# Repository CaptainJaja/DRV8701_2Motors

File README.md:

# Driver DRV8701 – Dual H-Bridge 40 V / 10 A (15 A peak)

> PCB designed with **KiCad** for driving **two brushed DC motors** up to 40 V / 10 A.
> Each channel uses a TI **DRV8701** driver paired with four **TPH1R403NL** power MOSFETs.
> The board integrates **encoder feedback** for PID control, as well as **current regulation** handled directly by the DRV8701.
> The current limit is set to **3 A**: above this value, the driver applies **PWM current chopping** to maintain the current below the set point.

---

## ⭐ Sponsor: PCBWay

This project was **sponsored by PCBWay**, who kindly provided the PCBs for prototyping.
The PCB quality is excellent and the support very responsive.

👉 **PCBWay Link:**

Thanks again to Liam and the PCBWay team for their support!

---

## Main Specifications

| Parameter                | Value                                        |
| ------------------------ | -------------------------------------------- |
| Supply voltage VM        | 7 – 40 V                                     |
| Continuous current/motor | 10 A (4-layer PCB, 1 oz copper)              |
| Peak current             | 15 A (≤ 100 ms)                              |
| Chopped current limit    | 3 A (via DRV8701)                            |
| Topology                 | 2 × full H-bridge (DRV8701 + 4 MOSFETs each) |
| Control signals          | PH / EN / nSLEEP (TTL 3.3 V / 5 V)           |
| LED indication           | **EN** (active when nSLEEP = HIGH)           |
| NeoPixel indication      | Battery status (>25 V / 23–25 V / <23 V)     |
| PCB dimensions           | 100 mm × 40 mm                               |

---

## Thermal Management

* DRV8701 **exposed pad** connected to the GND plane through thermal vias.
* **TPH1R403NL (SOP-Advance)** MOSFETs soldered onto a large copper area + internal plane for heat spreading.
* Bulk decoupling capacitors: **470 µF / 50 V**, low ESR.

---

## PCB Views

### Component side

### Bottom copper side

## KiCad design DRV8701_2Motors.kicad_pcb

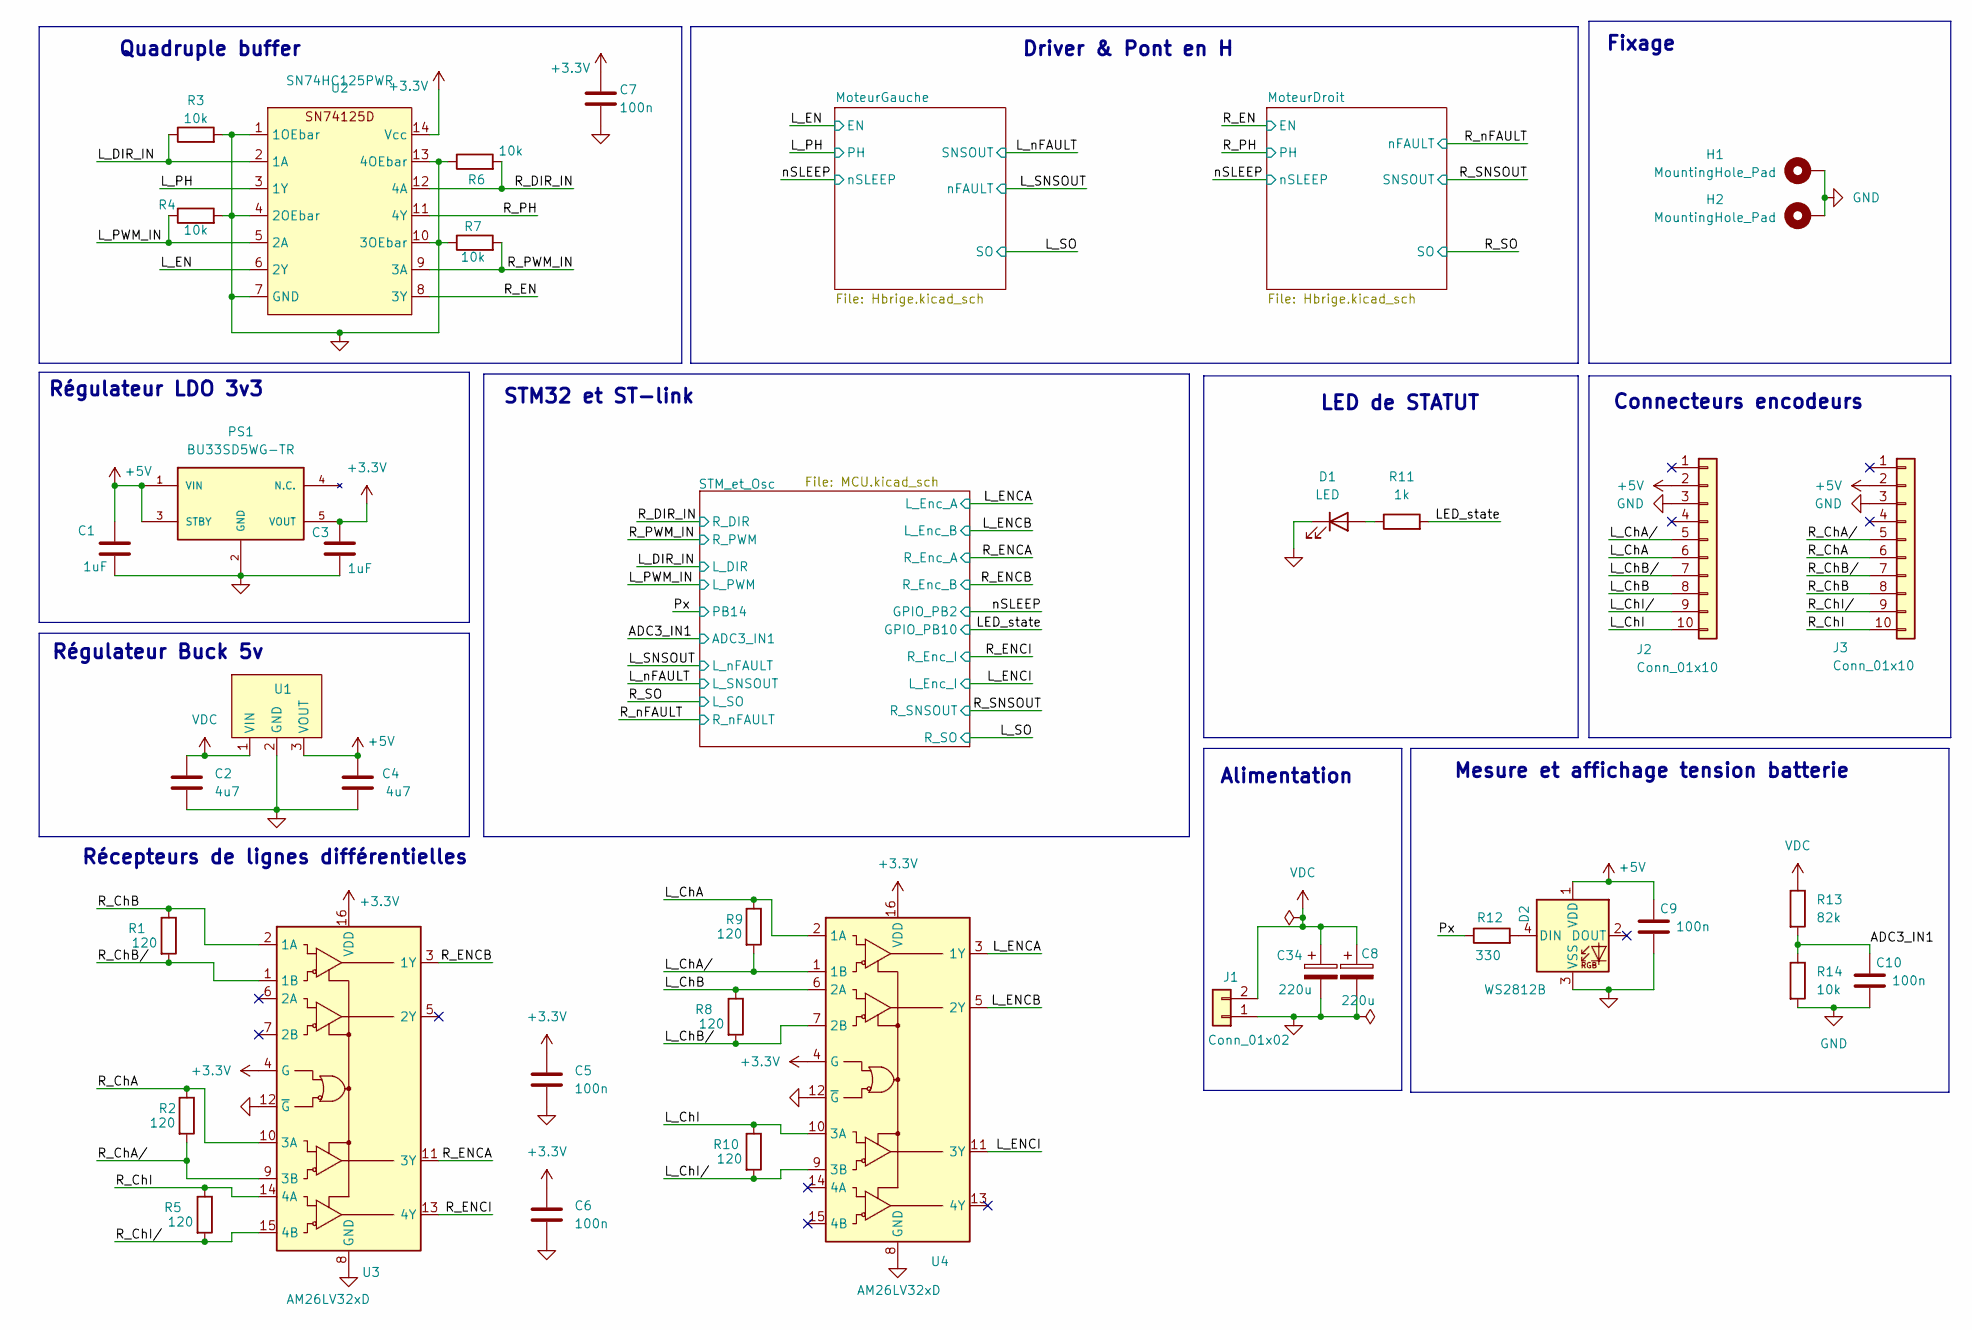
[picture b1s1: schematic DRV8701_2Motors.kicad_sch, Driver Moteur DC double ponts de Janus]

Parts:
C1, C3: 1uF; C_0603_1608Metric
C2: 4u7; C_1206_3216Metric
C4: 4u7; C_0603_1608Metric
C5, C6, C7, C9, C10: 100n; C_0402_1005Metric
C8, C34: 220u; ECA1HHG471
D1: LED; LED_0603_1608Metric_Pad1.05x0.95mm_HandSolder
D2: WS2812B; LED_WS2812B_PLCC4_5.0x5.0mm_P3.2mm
H1, H2: MountingHole_Pad; MountingHole_2.5mm_Pad
J1: Conn_01x02; KF301-5.0-2P
J2, J3: Conn_01x10; PinHeader_2x05_P1.27mm_Vertical_SMD
PS1: BU33SD5WG-TR; SOT95P280X125-5N; Mouser_Part_Number 755-BU33SD5WG-TR
R1, R2, R5, R8, R9, R10: 120; R_0402_1005Metric
R3, R4, R6, R7, R14: 10k; R_0402_1005Metric
R11: 1k; R_0402_1005Metric
R12: 330; R_0402_1005Metric
R13: 82k; R_0402_1005Metric
U1: StepDown3v3; MPN 173010x78
U2: SN74HC125PWR
U3, U4: AM26LV32xD; SOIC-16_3.9x9.9mm_P1.27mm

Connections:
+3.3V: C3.1, C5.1, C6.1, C7.1, PS1.5 (VOUT), U2.14 (Vcc), U3.4 (G), U3.16 (VDD), U4.4 (G), U4.16 (VDD); also elsewhere on the board
+5V: C1.1, C4.1, C9.2, D2.1 (VDD), J2.2, J3.2, PS1.1 (VIN), PS1.3 (STBY), U1.3 (VOUT)
/ADC3_IN1: C10.2, R13.2, R14.1; also elsewhere on the board
/LED_state: R11.2; also elsewhere on the board
/L_ChA: J2.6, R9.1, U4.2 (1A)
/L_ChA/: J2.5, R9.2, U4.1 (1B)
/L_ChB: J2.8, R8.1, U4.6 (2A)
/L_ChB/: J2.7, R8.2, U4.7 (2B)
/L_ChI: J2.10, R10.1, U4.10 (3A)
/L_ChI/: J2.9, R10.2, U4.9 (3B)
/L_DIR_IN: R3.1, U2.2 (1A); also elsewhere on the board
/L_EN: U2.6 (2Y); also elsewhere on the board
/L_ENCA: U4.3 (1Y); also elsewhere on the board
/L_ENCB: U4.5 (2Y); also elsewhere on the board
/L_ENCI: U4.11 (3Y); also elsewhere on the board
/L_PH: U2.3 (1Y); also elsewhere on the board
/L_PWM_IN: R4.1, U2.5 (2A); also elsewhere on the board
/Px: R12.1; also elsewhere on the board
/R_ChA: J3.6, R2.1, U3.10 (3A)
/R_ChA/: J3.5, R2.2, U3.9 (3B)
/R_ChB: J3.8, R1.1, U3.2 (1A)
/R_ChB/: J3.7, R1.2, U3.1 (1B)
/R_ChI: J3.10, R5.1, U3.14 (4A)
/R_ChI/: J3.9, R5.2, U3.15 (4B)
/R_DIR_IN: R6.2, U2.12 (4A); also elsewhere on the board
/R_EN: U2.8 (3Y); also elsewhere on the board
/R_ENCA: U3.11 (3Y); also elsewhere on the board
/R_ENCB: U3.3 (1Y); also elsewhere on the board
/R_ENCI: U3.13 (4Y); also elsewhere on the board
/R_PH: U2.11 (4Y); also elsewhere on the board
/R_PWM_IN: R7.2, U2.9 (3A); also elsewhere on the board
GND: C1.2, C2.2, C3.2, C4.2, C5.2, C6.2, C7.2, C8.2, C9.1, C10.1, C34.2, D1.1 (K), D2.3 (VSS), H1.1, H2.1, J1.1, J2.3, J3.3, PS1.2 (GND), R3.2, R4.2, R6.1, R7.1, R14.2, U1.2 (GND), U2.1 (1OEbar), U2.4 (2OEbar), U2.7 (GND), U2.10 (3OEbar), U2.13 (4OEbar), U3.8 (GND), U3.12 (~G), U4.8 (GND), U4.12 (~G); also elsewhere on the board
unnamed: D1.2 (A), R11.1
unnamed: D2.4 (DIN), R12.2
VDC: C2.1, C8.1, C34.1, J1.2, R13.1, U1.1 (VIN); also elsewhere on the board

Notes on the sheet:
STM32 et ST-link
Driver & Pont en H
Fixage
Quadruple buffer
Régulateur LDO 3v3
Connecteurs encodeurs
Alimentation
LED de STATUT
Récepteurs de lignes différentielles
Régulateur Buck 5v
Mesure et affichage tension batterie

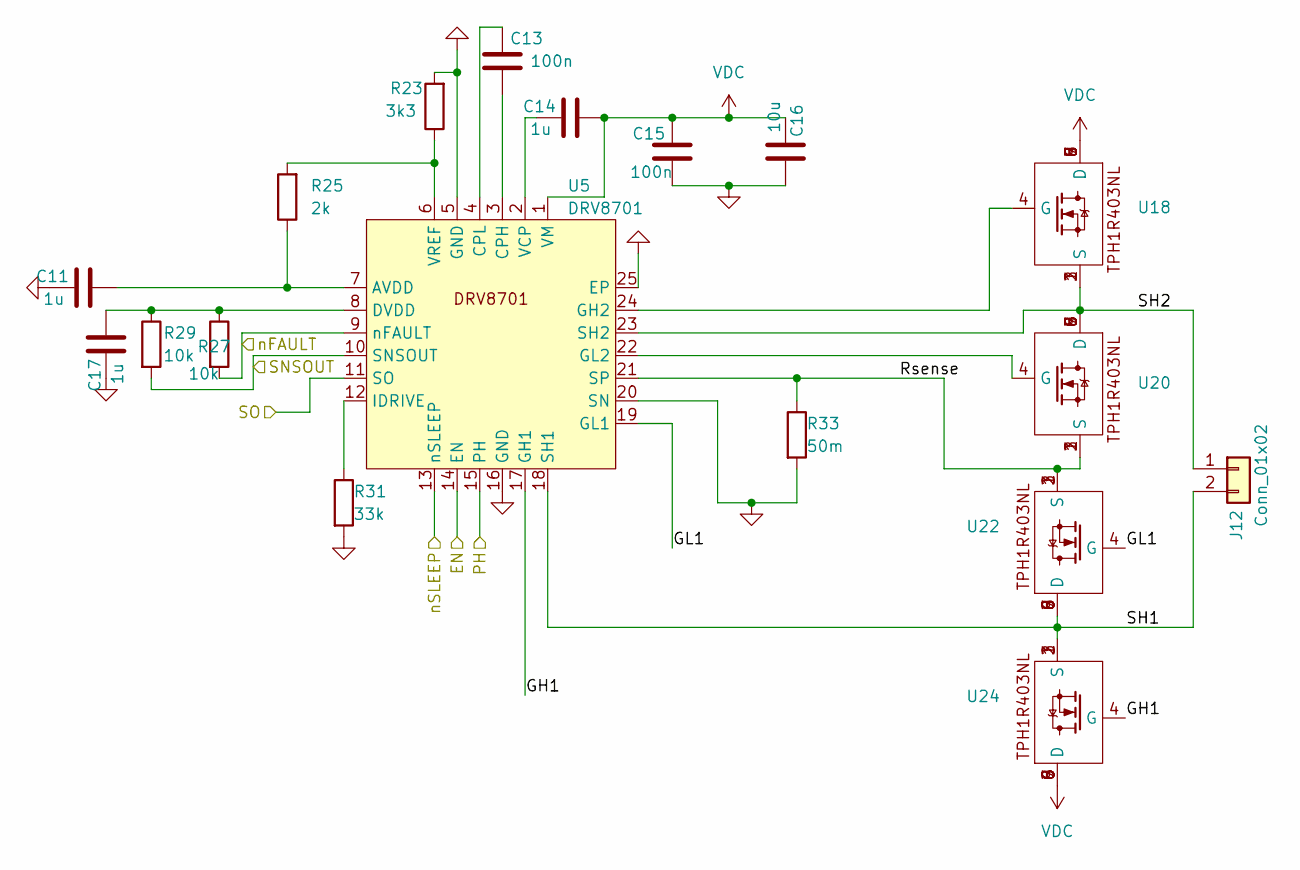
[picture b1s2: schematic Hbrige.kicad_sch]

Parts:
C11, C17: 1u; C_0603_1608Metric
C13, C15: 100n; C_0603_1608Metric
C14: 1u; C_0805_2012Metric
C16: 10u; C_1206_3216Metric
J12: Conn_01x02; KF301-5.0-2P
R23: 3k3; R_0402_1005Metric
R25: 2k; R_0402_1005Metric
R27, R29: 10k; R_0402_1005Metric
R31: 33k; R_0402_1005Metric
R33: 50m; R_2512_6332Metric
U5: DRV8701; DRV8701ERGER
U18, U20, U22, U24: TPH1R403NL; MPN TPH1R403NL

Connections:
/MoteurDroit/GH1: U5.17 (GH1), U24.4 (G)
/MoteurDroit/GL1: U5.19 (GL1), U22.4 (G)
/MoteurDroit/Rsense: R33.1, U5.21 (SP), U20.1 (S), U20.2 (S), U20.3 (S), U22.1 (S), U22.2 (S), U22.3 (S)
/MoteurDroit/SH1: J12.2, U5.18 (SH1), U22.5 (D), U22.6 (D), U22.7 (D), U22.8 (D), U22.9 (D), U24.1 (S), U24.2 (S), U24.3 (S)
/MoteurDroit/SH2: J12.1, U5.23 (SH2), U18.1 (S), U18.2 (S), U18.3 (S), U20.5 (D), U20.6 (D), U20.7 (D), U20.8 (D), U20.9 (D)
/R_EN: U5.14 (EN); also elsewhere on the board
/R_PH: U5.15 (PH); also elsewhere on the board
/R_SNSOUT: R29.2, U5.10 (SNSOUT); also elsewhere on the board
/R_SO: U5.11 (SO); also elsewhere on the board
/R_nFAULT: R27.2, U5.9 (nFAULT); also elsewhere on the board
/nSLEEP: U5.13 (nSLEEP); also elsewhere on the board
GND: C11.2, C15.1, C16.1, C17.2, R23.2, R31.2, R33.2, U5.5 (GND), U5.16 (GND), U5.20 (SN), U5.25 (EP); also elsewhere on the board
unnamed: C11.1, R25.1, U5.7 (AVDD)
unnamed: C13.1, U5.3 (CPH)
unnamed: C13.2, U5.4 (CPL)
unnamed: C17.1, R27.1, R29.1, U5.8 (DVDD)
unnamed: R31.1, U5.12 (IDRIVE)
unnamed: C14.2, U5.2 (VCP)
unnamed: R23.1, R25.2, U5.6 (VREF)
unnamed: U5.24 (GH2), U18.4 (G)
unnamed: U5.22 (GL2), U20.4 (G)
VDC: C14.1, C15.2, C16.2, U5.1 (VM), U18.5 (D), U18.6 (D), U18.7 (D), U18.8 (D), U18.9 (D), U24.5 (D), U24.6 (D), U24.7 (D), U24.8 (D), U24.9 (D); also elsewhere on the board

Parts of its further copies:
C12, C18: 1u; C_0603_1608Metric
C19, C21: 100n; C_0603_1608Metric
C20: 1u; C_0805_2012Metric
C22: 10u; C_1206_3216Metric
J13: Conn_01x02; KF301-5.0-2P
R24: 3k3; R_0402_1005Metric
R26: 2k; R_0402_1005Metric
R28, R30: 10k; R_0402_1005Metric
R32: 33k; R_0402_1005Metric
R34: 50m; R_2512_6332Metric
U10: DRV8701; DRV8701ERGER
U19, U21, U23, U25: TPH1R403NL; MPN TPH1R403NL

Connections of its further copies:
/L_EN: U10.14 (EN); also elsewhere on the board
/L_PH: U10.15 (PH); also elsewhere on the board
/L_SNSOUT: R28.2, U10.9 (nFAULT); also elsewhere on the board
/L_SO: U10.11 (SO); also elsewhere on the board
/L_nFAULT: R30.2, U10.10 (SNSOUT); also elsewhere on the board
/MoteurGauche/GH1: U10.17 (GH1), U25.4 (G)
/MoteurGauche/GL1: U10.19 (GL1), U23.4 (G)
/MoteurGauche/Rsense: R34.1, U10.21 (SP), U21.1 (S), U21.2 (S), U21.3 (S), U23.1 (S), U23.2 (S), U23.3 (S)
/MoteurGauche/SH1: J13.2, U10.18 (SH1), U23.5 (D), U23.6 (D), U23.7 (D), U23.8 (D), U23.9 (D), U25.1 (S), U25.2 (S), U25.3 (S)
/MoteurGauche/SH2: J13.1, U10.23 (SH2), U19.1 (S), U19.2 (S), U19.3 (S), U21.5 (D), U21.6 (D), U21.7 (D), U21.8 (D), U21.9 (D)
/nSLEEP: U10.13 (nSLEEP); also elsewhere on the board
GND: C12.2, C18.2, C21.1, C22.1, R24.2, R32.2, R34.2, U10.5 (GND), U10.16 (GND), U10.20 (SN), U10.25 (EP); also elsewhere on the board
unnamed: C12.1, R26.1, U10.7 (AVDD)
unnamed: C19.1, U10.3 (CPH)
unnamed: C19.2, U10.4 (CPL)
unnamed: C18.1, R28.1, R30.1, U10.8 (DVDD)
unnamed: U10.24 (GH2), U19.4 (G)
unnamed: U10.22 (GL2), U21.4 (G)
unnamed: R32.1, U10.12 (IDRIVE)
unnamed: C20.2, U10.2 (VCP)
unnamed: R24.1, R26.2, U10.6 (VREF)
VDC: C20.1, C21.2, C22.2, U10.1 (VM), U19.5 (D), U19.6 (D), U19.7 (D), U19.8 (D), U19.9 (D), U25.5 (D), U25.6 (D), U25.7 (D), U25.8 (D), U25.9 (D); also elsewhere on the board

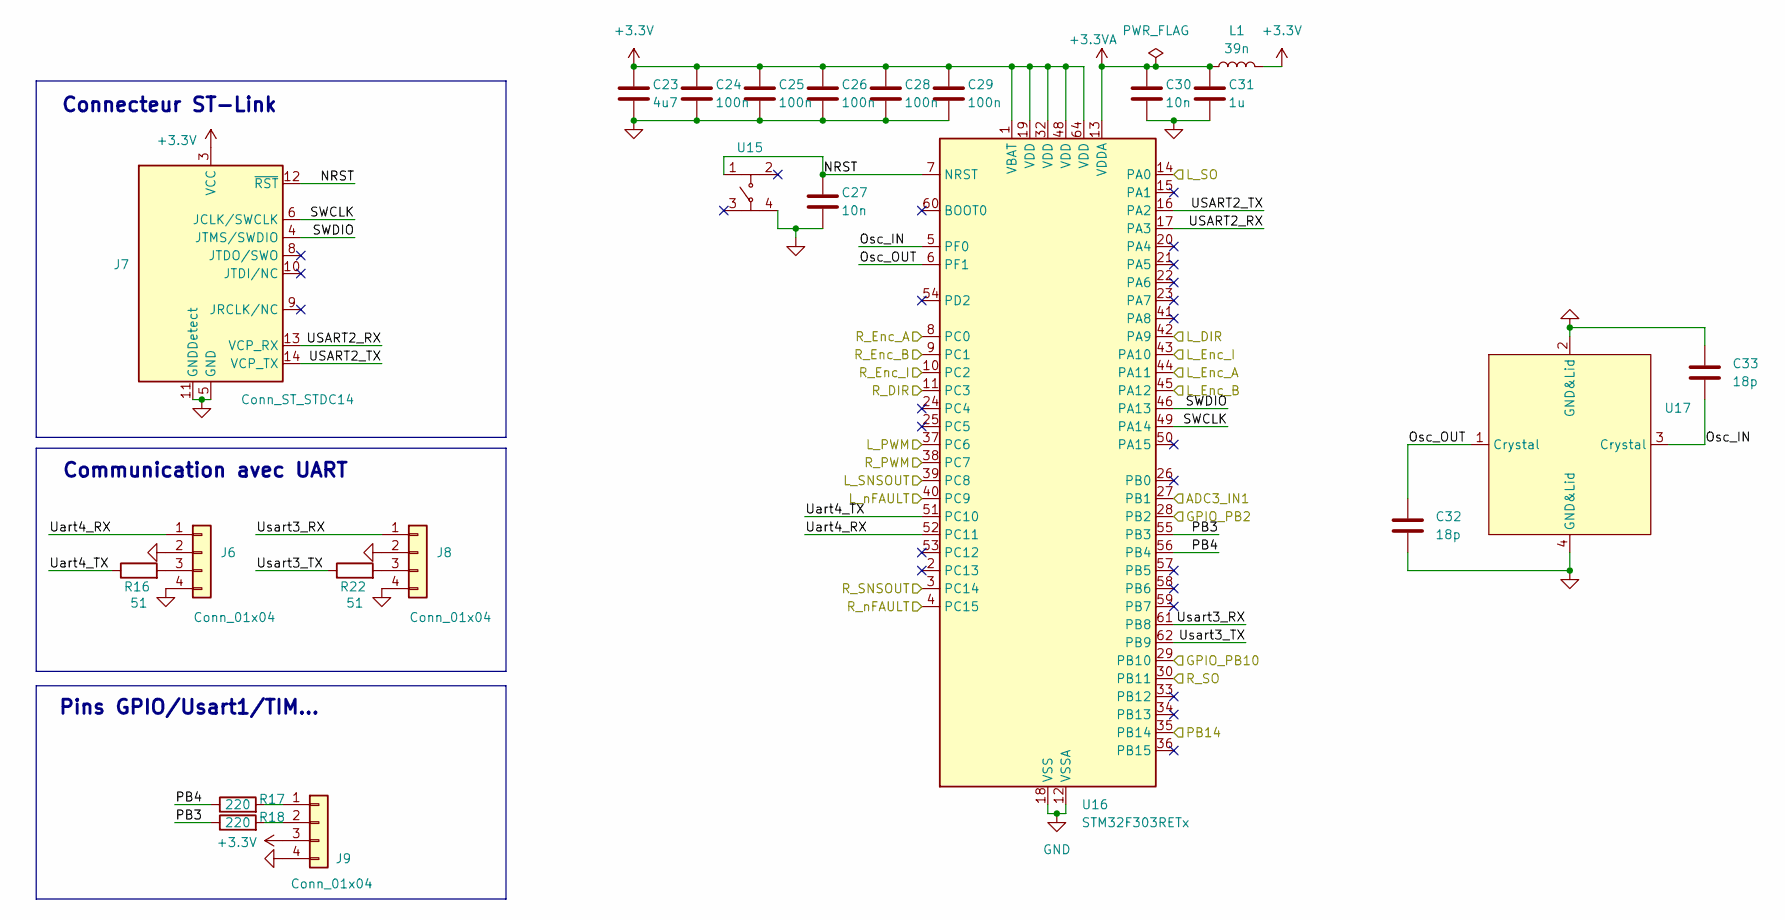
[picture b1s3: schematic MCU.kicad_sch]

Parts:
C23: 4u7; C_0402_1005Metric
C24, C25, C26, C28, C29: 100n; C_0402_1005Metric
C27, C30: 10n; C_0402_1005Metric
C31: 1u; C_0402_1005Metric
C32, C33: 18p; C_0603_1608Metric
J6, J8: Conn_01x04; JST_EH_B4B-EH-A_1x04_P2.50mm_Vertical
J7: Conn_ST_STDC14; PinHeader_2x07_P1.27mm_Vertical_SMD
J9: Conn_01x04; PinHeader_1x04_P2.54mm_Vertical
L1: 39n; L_0603_1608Metric
R16, R22: 51; R_0402_1005Metric
R17, R18: 220; R_0402_1005Metric
U15: WS-TASU SMT Tact Switch 4.7x3.5 mm side push
U16: STM32F303RETx; LQFP-64_10x10mm_P0.5mm
U17: Crystal_SMD_7050-4Pin_7.0x5.0mm

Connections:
+3.3V: C23.1, C24.1, C25.1, C26.1, C28.1, C29.1, J7.3 (VCC), J9.3, L1.2, U16.1 (VBAT), U16.19 (VDD), U16.32 (VDD), U16.48 (VDD), U16.64 (VDD); also elsewhere on the board
+3.3VA: C30.1, C31.1, L1.1, U16.13 (VDDA)
/ADC3_IN1: U16.27 (PB1); also elsewhere on the board
/LED_state: U16.29 (PB10); also elsewhere on the board
/L_DIR_IN: U16.42 (PA9); also elsewhere on the board
/L_ENCA: U16.44 (PA11); also elsewhere on the board
/L_ENCB: U16.45 (PA12); also elsewhere on the board
/L_ENCI: U16.43 (PA10); also elsewhere on the board
/L_PWM_IN: U16.37 (PC6); also elsewhere on the board
/L_SNSOUT: U16.40 (PC9); also elsewhere on the board
/L_SO: U16.30 (PB11); also elsewhere on the board
/L_nFAULT: U16.39 (PC8); also elsewhere on the board
/Px: U16.35 (PB14); also elsewhere on the board
/R_DIR_IN: U16.11 (PC3); also elsewhere on the board
/R_ENCA: U16.8 (PC0); also elsewhere on the board
/R_ENCB: U16.9 (PC1); also elsewhere on the board
/R_ENCI: U16.10 (PC2); also elsewhere on the board
/R_PWM_IN: U16.38 (PC7); also elsewhere on the board
/R_SNSOUT: U16.3 (PC14); also elsewhere on the board
/R_SO: U16.14 (PA0); also elsewhere on the board
/R_nFAULT: U16.4 (PC15); also elsewhere on the board
/STM_et_Osc/NRST: C27.1, J7.12 (~RST), U15.1, U16.7 (NRST)
/STM_et_Osc/Osc_IN: C33.2, U16.5 (PF0), U17.3 (Crystal)
/STM_et_Osc/Osc_OUT: C32.1, U16.6 (PF1), U17.1 (Crystal)
/STM_et_Osc/PB3: R18.1, U16.55 (PB3)
/STM_et_Osc/PB4: R17.1, U16.56 (PB4)
/STM_et_Osc/SWCLK: J7.6 (JCLK/SWCLK), U16.49 (PA14)
/STM_et_Osc/SWDIO: J7.4 (JTMS/SWDIO), U16.46 (PA13)
/STM_et_Osc/USART2_RX: J7.13 (VCP_RX), U16.17 (PA3)
/STM_et_Osc/USART2_TX: J7.14 (VCP_TX), U16.16 (PA2)
/STM_et_Osc/Uart4_RX: J6.1, U16.52 (PC11)
/STM_et_Osc/Uart4_TX: R16.1, U16.51 (PC10)
/STM_et_Osc/Usart3_RX: J8.1, U16.61 (PB8)
/STM_et_Osc/Usart3_TX: R22.1, U16.62 (PB9)
/nSLEEP: U16.28 (PB2); also elsewhere on the board
GND: C23.2, C24.2, C25.2, C26.2, C27.2, C28.2, C29.2, C30.2, C31.2, C32.2, C33.1, J6.2, J6.4, J7.5 (GND), J7.7 (GND), J7.11 (GNDDetect), J8.2, J8.4, J9.4, U15.4, U16.12 (VSSA), U16.18 (VSS), U16.31 (VSS), U16.47 (VSS), U16.63 (VSS), U17.2 (GND&Lid), U17.4 (GND&Lid); also elsewhere on the board
unnamed: J6.3, R16.2
unnamed: J8.3, R22.2
unnamed: J9.1, R17.2
unnamed: J9.2, R18.2

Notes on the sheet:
Pins GPIO/Usart1/TIM...
Communication avec UART
Connecteur ST-Link

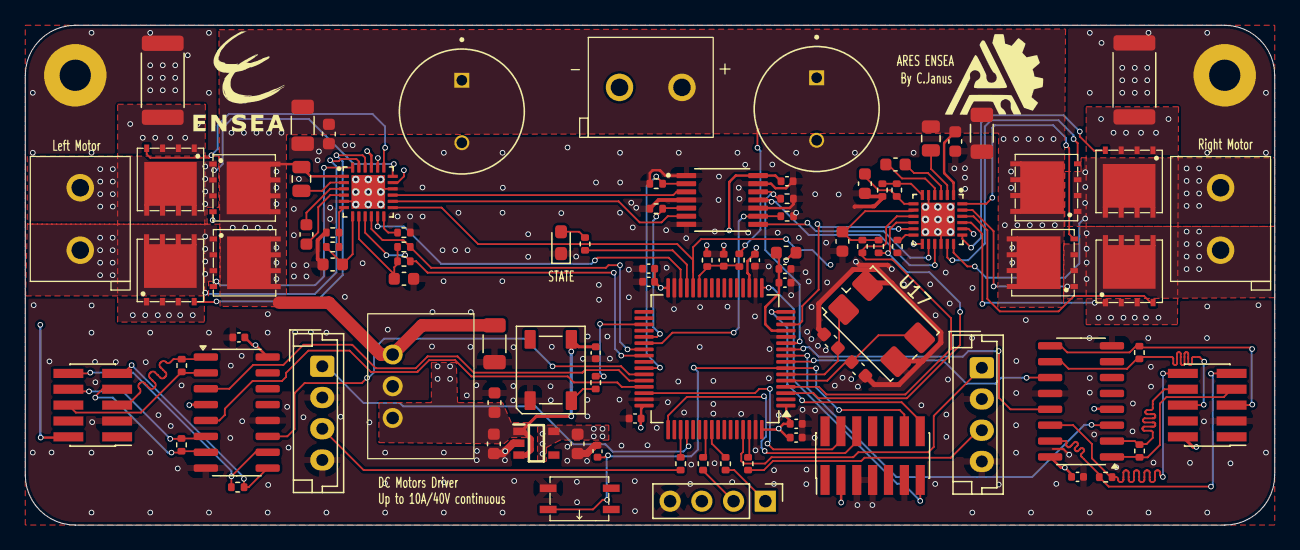
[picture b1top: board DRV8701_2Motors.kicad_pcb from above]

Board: 4 copper layers, 100.0 x 40.0 mm, 96 parts (0 on the bottom side), 88 nets.

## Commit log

2025-05-11 Premier import du driver DRV8701 (2 moteurs)
2025-05-11 modif README
2025-05-11 modif épaisseur cuivre
2025-05-11 petite correction sur les remplissages de zone
2025-06-14 PCB V2 : adapté pour les moteurs maxons, avec l'asservissement directement dessus. Finalisation du schématique
2025-06-16 finalisation schematique
2025-06-16 reintroduction des mosfet (au lieu des demi-ponts en H), début routage
2025-06-17 maj PCB
2025-06-17 finalisation PCB
2025-06-17 MAJ README
2025-06-18 MAJ vias thermiques des drivers
2025-06-18 final push
2025-06-21 finalisation V2 -- manque plus que les vias gnd
2025-06-21 finalisation PCB v2
2025-06-28 alignement des drv
2025-06-28 maj README img
2025-07-01 gerber avec reduction 15% du paste
2025-09-05 modif footprints des condo de puissance
2025-09-16 V2 Driver-- avec control de courant
2025-09-16 maj images README
2025-09-19 maj readme, supprimé deux vias non utiles
2025-09-19 final push--tous les composants sur le Front
2025-09-20 alignement connecteur, changement connecteur
2025-09-20 maj readme driver
2025-10-08 last push
